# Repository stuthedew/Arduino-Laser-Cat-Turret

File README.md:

# Arduino-Laser-Cat-Turret
Arduino-based laser turret/automatic cat toy using a pan-tilt rig ([https://www.adafruit.com/products/1967](https://www.adafruit.com/products/1967)) and laser diode ([https://www.adafruit.com/products/1054](https://www.adafruit.com/products/1054)). Random laser path, speed and pauses determined by homebrew Markov chain algorithm.

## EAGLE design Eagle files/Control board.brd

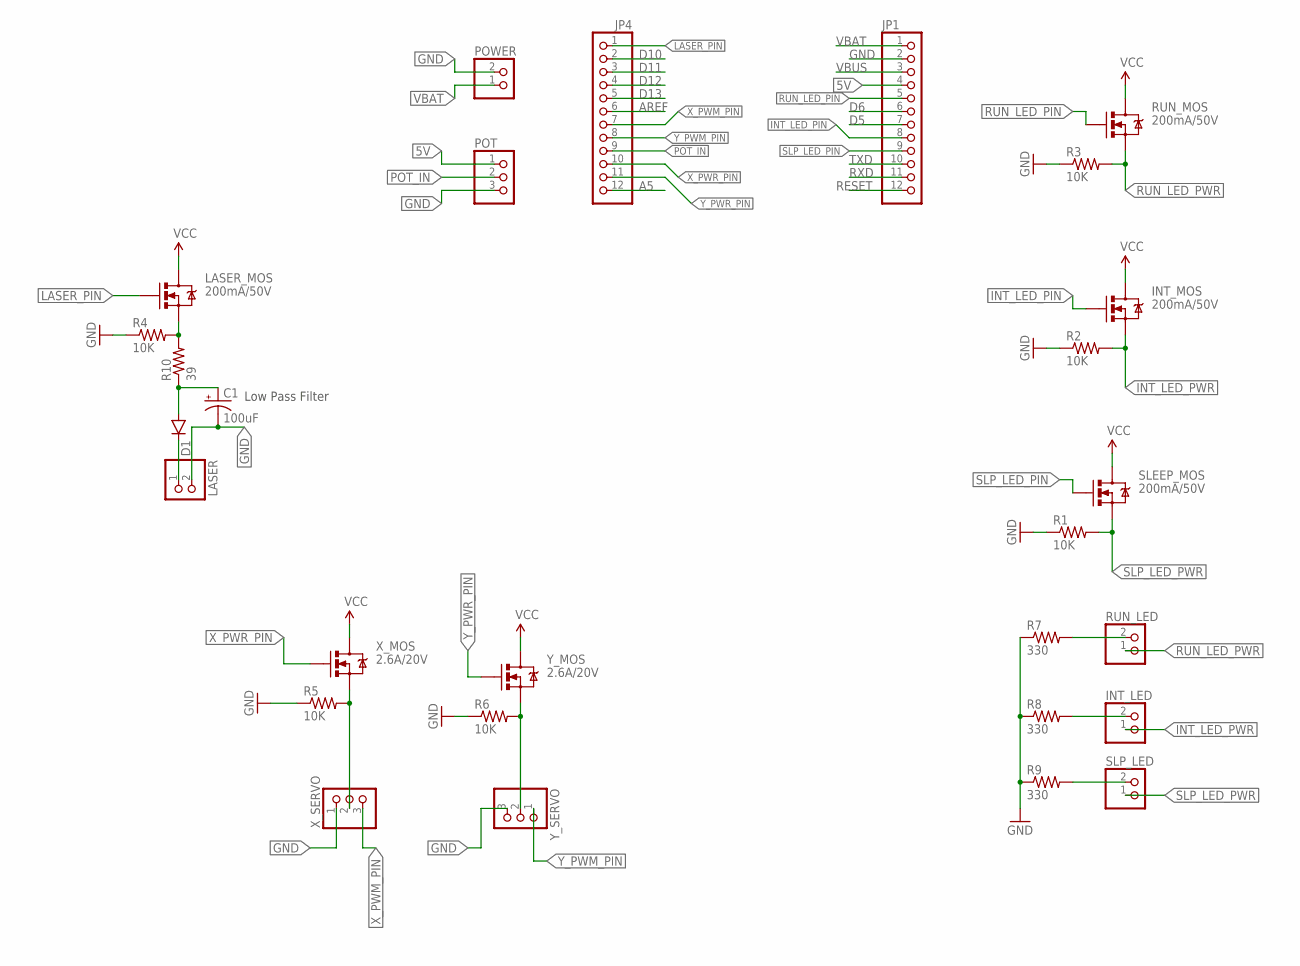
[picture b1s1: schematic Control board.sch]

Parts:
C1: 100uF; EIA7343
D1: DIODESOD123; SOD-123
INT_LED: JST_2PIN-SMT-RA; JST-PH-2-SMT-RA
INT_MOS: 200mA/50V; SOT23-3
JP1, JP4: PINHD-1X12-CB; 1X12-CB
LASER: JST_2PIN-SMT-RA; JST-PH-2-SMT-RA
LASER_MOS: 200mA/50V; SOT23-3
POT: JST_3PIN; JSTPH3
POWER: JST_2PIN-SMT-RA; JST-PH-2-SMT-RA
R1, R2, R3, R4, R5, R6: 10K; 0603-RES
R7, R8, R9: 330; 0603-RES
R10: 39; 0603-RES
RUN_LED: JST_2PIN-SMT-RA; JST-PH-2-SMT-RA
RUN_MOS: 200mA/50V; SOT23-3
SLEEP_MOS: 200mA/50V; SOT23-3
SLP_LED: JST_2PIN-SMT-RA; JST-PH-2-SMT-RA
X_MOS: 2.6A/20V; SOT23-3
X_SERVO: PINHD-1X3; 1X03
Y_MOS: 2.6A/20V; SOT23-3
Y_SERVO: PINHD-1X3; 1X03

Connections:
5V: JP1.4, POT.1
A5: JP4.12
AREF: JP4.6
D5: JP1.7
D6: JP1.6
D10: JP4.2
D11: JP4.3
D12: JP4.4
D13: JP4.5
GND: C1.C (-), JP1.2, LASER.2 (1), POT.3, POWER.2 (1), R1.1, R2.1, R3.1, R4.1, R5.1, R6.1, R7.1, R8.1, R9.1, X_SERVO.1, Y_SERVO.3
INT_LED_PIN: INT_MOS.1 (G), JP1.8
INT_LED_PWR: INT_LED.1 (2), INT_MOS.2 (S), R2.2
LASER_PIN: JP4.1, LASER_MOS.1 (G)
LASER_PWR: LASER_MOS.2 (S), R4.2, R10.2
unnamed: C1.A (+), D1.A, R10.1
unnamed: D1.C, LASER.1 (2)
unnamed: R6.2, Y_MOS.2 (S), Y_SERVO.2
unnamed: R5.2, X_MOS.2 (S), X_SERVO.2
unnamed: R7.2, RUN_LED.2 (1)
unnamed: INT_LED.2 (1), R8.2
unnamed: R9.2, SLP_LED.2 (1)
POT_IN: JP4.9, POT.2
RESET: JP1.12
RUN_LED_PIN: JP1.5, RUN_MOS.1 (G)
RUN_LED_PWR: R3.2, RUN_LED.1 (2), RUN_MOS.2 (S)
RXD: JP1.11
SLP_LED_PIN: JP1.9, SLEEP_MOS.1 (G)
SLP_LED_PWR: R1.2, SLEEP_MOS.2 (S), SLP_LED.1 (2)
TXD: JP1.10
VBAT: INT_MOS.3 (D), JP1.1, LASER_MOS.3 (D), POWER.1 (2), RUN_MOS.3 (D), SLEEP_MOS.3 (D), X_MOS.3 (D), Y_MOS.3 (D)
VBUS: JP1.3
X_PWM_PIN: JP4.7, X_SERVO.3
X_PWR_PIN: JP4.10, X_MOS.1 (G)
Y_PWM_PIN: JP4.8, Y_SERVO.1
Y_PWR_PIN: JP4.11, Y_MOS.1 (G)

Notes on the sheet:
Low Pass Filter

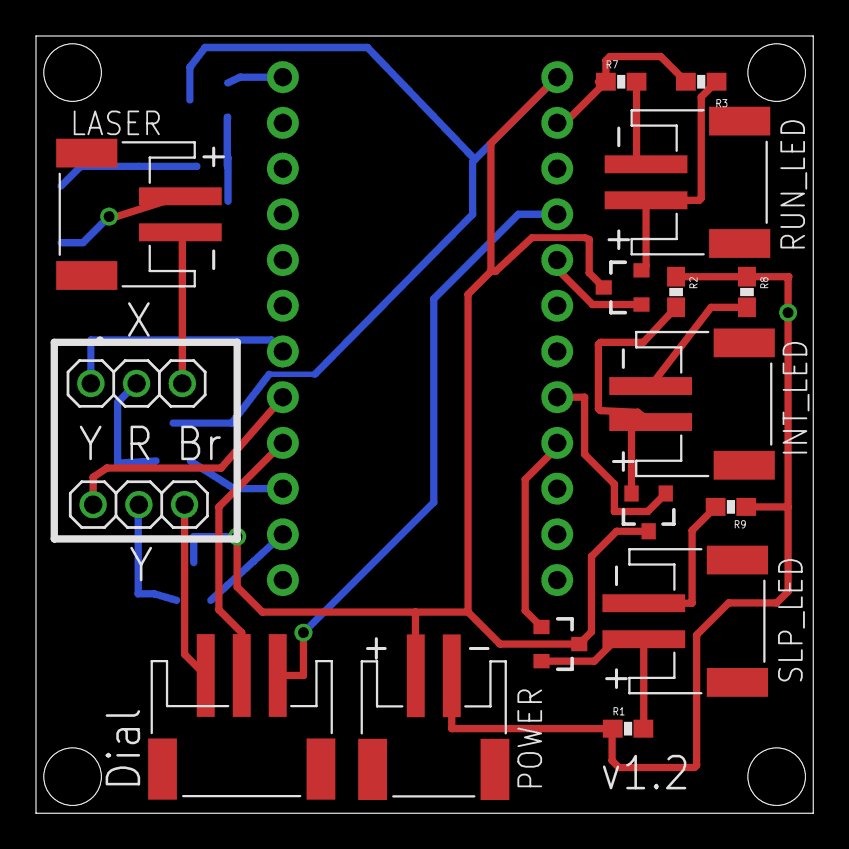
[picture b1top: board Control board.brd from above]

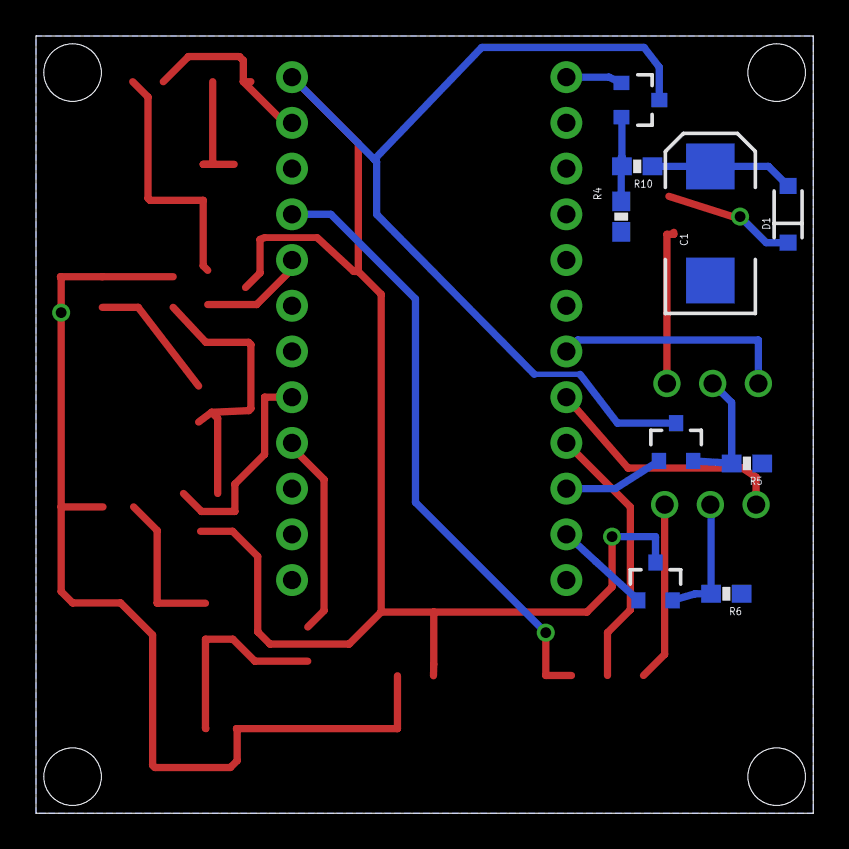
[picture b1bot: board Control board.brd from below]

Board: 2 copper layers, 43.2 x 43.2 mm, 28 parts (9 on the bottom side), 23 nets.

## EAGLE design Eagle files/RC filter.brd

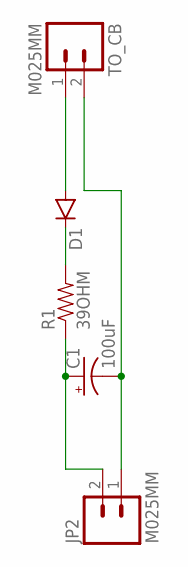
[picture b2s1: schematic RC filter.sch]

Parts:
C1: 100uF; EIA7343
D1: DIODESMA; SMA-DIODE
JP2: M025MM; SCREWTERMINAL-5MM-2
R1: 39OHM; 0603
TO_CB: M025MM; SCREWTERMINAL-5MM-2

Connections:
GND: C1.C (-), JP2.1, TO_CB.2
unnamed: D1.C, R1.2
V_IN: D1.A, TO_CB.1
V_OUT: C1.A (+), JP2.2, R1.1

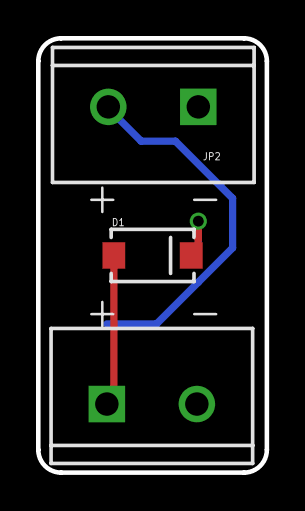
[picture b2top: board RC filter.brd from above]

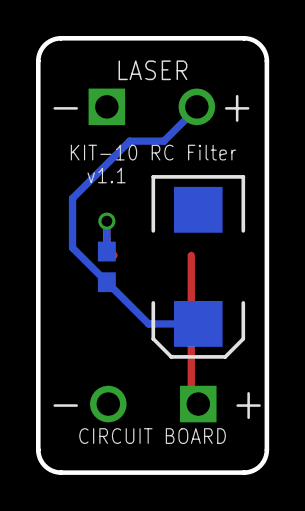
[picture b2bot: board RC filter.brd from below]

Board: 2 copper layers, 12.7 x 24.1 mm, 5 parts (2 on the bottom side), 4 nets.

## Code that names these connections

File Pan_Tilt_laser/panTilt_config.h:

#pragma once

#include "Arduino.h"


#define EMBED


//#define SERIAL_DEBUG


#ifdef SERIAL_DEBUG
  #define BAUD_RATE 9600
#endif

#define DIRECTION_CHANGE_PROBABILITY 15


// Servo pins
#define X_PWR_PIN   A3
#define Y_PWR_PIN   A4
#define SERVO_X_PIN A0    // PWM Pins
#define SERVO_Y_PIN A1

//LED power pins
#define POWER_PIN 8 // Power lED pin
#define CONT_PIN  4 // Continuous LED pin
#define INT_PIN   3 // Intermittent LED pin

#define LASER_PIN 9

#define DIAL_PIN A2


#ifdef SERIAL_DEBUG

#define MY_SERIAL Serial


#endif

// Global Run Mode enum
typedef enum {
  MODE_OFF = 0      ,
  MODE_CONTINUOUS   ,
  MODE_INTERMITTENT ,
  MODE_SLEEP
}runmode_e;

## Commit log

2014-10-14 Clean up
2014-10-14 Changed Markov Speed
2014-10-14 Added Markov Speed Back
2014-10-14 Added delay variable
2014-10-14 Added check when switching directions.
    Only switch direction if past max/min range AND direction going away
    from normal range.
2014-10-14 Added Markov Pause
2014-10-14 Tweaked pause frequency
2014-10-14 Changed pause frequencies
2014-10-14 Added semicolon
2014-10-14 More Pause tweaks
2014-10-14 More Tweaks
2014-10-14 Increased delay to allow servo movement.
2014-10-14 Added file headers
2014-10-14 Removed debugging code from master
2014-10-14 Added updated version history
2014-10-14 Added Mac git ignore file
    https://github.com/github/gitignore/blob/master/Global/OSX.gitignore
2014-10-14 Cleaned up formatting
2014-10-14 Cleaned Formatting
2014-10-14 Cleaned dev
2014-10-14 Cleaned up conflicts
2014-10-14 Defined direction change probability
    Change direction change probability from variable to definition.
2014-10-14 Revert "Clean up"
    This reverts commit 1cc41362a7edf90dbaecc19a8334832e626d1877.
2014-10-15 Added Heartbeat pulse and fixed value overflow
2014-10-15 Tweaks
2014-10-15 Shortened heartbeat delay
2014-10-15 Added rollover handling in sleep function
2014-10-15 Fixed typo in rollover handling
2014-10-15 tweaked rollover handling
2014-10-16 Added delay back between servos and clean up
2014-10-16 Decreased pause probability
2014-10-19 changed sleep function to require seconds
    instead of minutes
2014-10-19 Added laser Shake
2014-10-19 Added shake to main program
2014-10-19 Removed delay from shake and added variable
2014-10-19 Removed Y shake and lowered speed
2014-10-19 Added markov shake
2014-10-19 Probability tweaks
2014-10-19 More probability tweaks
2014-10-19 Added probability adjust
2014-10-19 added minimum probability adjust
2014-10-19 tweaked y probability adjust
2014-10-19 adjusted shake probability
2014-10-19 Adjusted max speed
2014-10-19 Adjusted mid speed
2014-10-20 Changed probability polling frequency
2014-10-20 Added random seed
2014-10-20 Updated version
2014-10-25 Updated Pins
2014-10-25 Added switch code
2014-10-26 Added switch class
2014-10-26 Cleaning
2014-10-26 Fixed never completing debounce function
2014-10-26 Fixed debounce bug
2014-10-26 Fixed bug
2014-10-26 Added starting delay for stability
2014-10-26 Bumped version
2014-10-26 Added starting servo centering
2014-10-26 Minor tweaks
    Changed speed
2014-10-26 Added rollover check
2014-10-26 Moved random seed to random eval code
2014-10-26 Changed analog read pin for random seed
2014-10-26 Changed sleep angle
2014-10-26 Fixed typo
2014-10-27 Moved scheduler to test folder
2014-10-28 Working scheduler and task classes
2014-10-28 Added gaussian random number and scheduler
2014-10-28 Updated pause variance
2014-10-28 Cleanup and updated license
2014-10-28 Updated heartbeat interval
2014-10-28 Switched speed/direction control to scheduler
2014-10-29 Change the average time to sleep to 10 minutes
2014-10-29 Added more vector functions
2014-10-29 More functions
2014-10-29 Deleted test File
2014-10-29 Deleted unused function
2014-10-30 Added magSq function
2014-10-30 Merged Vector with AngleCalc
2014-10-30 Start position-based calculation
2014-10-30 Tweak
2014-10-30 Changed Vector to system library
2014-11-01 Use fastTrig
2014-11-01 Accuracy checking
2014-11-11 Probability and time tweaks
2014-11-11 Adjusted shake delay
2014-11-11 Adding structs and linked list
2014-11-11 Added Markov handler using linked lists
2014-11-11 Clean up and bumped version
2014-11-11 Set shake state to Markov handler.
2014-11-12 Tweaks and clean up
2014-11-12 Cleaned up old unused functions
2014-11-12 Decreased average pause time
    Decreased average pause time and cleaned up shake probabilities.
2014-11-12 Switched #ifdef #define to #pramga once
2014-11-12 Changed version number from 1.0 to 0.0.1
2014-11-12 Fixed sleep/switch bug #2
    Program now returns from sleep mode once switch is off and resumes when
    switch is turned on again.
2014-11-14 fixed compiling error due old variables.
2014-11-14 Partial conversion to custom namespace
    Still problems with stuPanTilt namespace use breaking things.
2014-11-14 Finish namespace
2014-11-14 Removed unnecessary Markov begin function
2014-11-28 Added schematic from adafruit
2014-11-28 Added dial control and LED display
2014-11-29 Removed namespace and added modes
2014-11-29 Working
2014-11-30 Added board file
2014-11-30 Board Tweaks
2014-12-01 Board work
2014-12-01 Modification for present.
2014-12-01 Removed unneeded includes
2014-12-01 Added base Event class and timer class
    Timer and Task classes are now derived from Event class
2014-12-01 Base Event class will compile but not yet tested
2014-12-01 Tweaked timer functions
2014-12-02 Routed board
2014-12-02 Added Servo power control
2014-12-02 Aesthetic tweaks
2014-12-02 Modified keywords and added rotary adapter board
2014-12-02 Removed Rotary switch board file
    Not working with OSHpark. Will troubleshoot later.
2014-12-02 Added data sheet for rotary switch
2014-12-04 Converting control to master class control
2014-12-05 Moved more to main control class
2014-12-05 Renamed datasheets
2014-12-06 Worked on scheduling led blinks
2014-12-09 Tweaks and added debug info
2014-12-09 Work
2014-12-09 Transferred pause and sleep task to main class
2014-12-09 Cleaned up replaced code.
2014-12-10 Clean up and tweaks
2014-12-10 More work
2014-12-10 Added back timing functions to ino file.
    Will use as template for timing
2014-12-10 Modified panTilt callback
2014-12-10 Cleaned up old tasks
    Remove after testing.
2014-12-11 Tweaked filtered analogRead function
2014-12-11 Added documentation to settings file
2014-12-13 Debugging
2014-12-13 Working mode and state switching!!!
2014-12-13 Version bump
2014-12-15 Working version and added faceplate text.
2014-12-15 Added readMicroseconds function and delay calc
2014-12-15 Moved servo delay to servo lib
2014-12-15 Removed extra delay
2014-12-15 Faceplate modification.
2014-12-15 Replaced loop delay with timer.
2014-12-15 Activated Serial debug
2014-12-15 Changed Event::run to pure virtual function.
2014-12-18 Working version
2014-12-18 Fixed pause time.
2014-12-18 Added pause without laser
2014-12-18 Tweaks
    Final version
2014-12-18 Fixed bug where pauseTask ran while off.
    Version bump.
2014-12-18 Tweaked servo Y min position.
2014-12-20 Tweaked Servo min/max
2014-12-20 Fixed attempted NULL pointer dereference
2014-12-20 Fixed pauseTask reset in main
2014-12-25 Fixed copy/paste error
2014-12-25 Added include to Arduino.h
2015-01-02 Create gh-pages branch via GitHub
2015-01-02 Serial Tweaks
2015-01-02 Merge branch 'Leah'
    Conflicts:
    Pan_Tilt_laser/Pan_Tilt_laser.ino
    Pan_Tilt_laser/stuServo.cpp
2015-01-02 Fixed conflicts
2015-01-02 Updated Keywords
2015-01-02 Added project photos
2015-01-02 Added test html page
2015-01-02 Tweaks to test page
2015-01-02 Version change
2015-01-02 Bump
2015-01-02 Switched to Jekyll-based page
2015-01-02 Tweaked file structure
2015-01-02 Markdown tweaks and timezone support
2015-01-03 Page tweaks
2015-01-03 Path tweaks to run on Github
2015-01-03 Ibid
2015-01-03 Added Navigation
2015-01-03 Added navigation bar
2015-01-03 Highlight nav buttons
2015-01-03 Changed picture
2015-01-03 Added more pages
2015-01-03 Tweaks to layout
2015-01-03 Removed permalink from index file
2015-01-05 Updated .gitignore
2015-02-06 Added images
2015-02-06 Removed unused file
2015-02-06 Added board version number
2015-02-06 Tweaked Board
2015-02-06 Changed file names
2015-02-15 added reverse diode protection on laser
2015-02-15 tweaked gitignore for eagle backups
2015-02-18 Changed screw terminal to 5.08 mm layout
    Bumped board to v1.1
2016-03-04 Revert "Merge branch 'master' into AngleCalc"
    This reverts commit c8a51e57248cddb0e953d0333ecdb938653df7a6, reversing
    changes made to 495443ae64bd3a2f187793db6e1e9aa18b25b567.
2016-03-04 Ignored sass and bt sync
2016-03-04 ignore .class files
2016-03-04 test
2016-03-04 Beautify-ed
2016-09-18 Create Kit-10 Run

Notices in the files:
parts and their libraries:
SparkFun-DiscreteSemi: Licensing: Creative Commons ShareAlike 4.0 International - https://creativecommons.org/licenses/by-sa/4.0
